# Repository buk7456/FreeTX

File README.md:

# FreeTX
Open source radio control system for almost anything.  
Remotely operate model airplanes, multicopters, helicopters, boats, land vehicles, robots, animatronics, etc.

## Main features
- 20 fully proportional RC channels, each encoded with 10 bits.
- Configurable RC channel output signal format.
- Update rate of 50x per second for all RC channels.
- Receiver binding, adjustable RF power, frequency hopping.
- Reverse, subtrim, endpoints, failsafe, dual rates and expo, custom curves, flight modes.
- Powerful mixer system, logical switches, function generators, counters, timers.
- Telemetry, alarms, warnings, notifications, home screen widgets, custom splash screen, etc.
- Model memory, I2C EEPROM and SD card supported. Model types, context-aware nomenclature.
- Intuitive user interface.

## Hardware and Schematics
The transmitter and receiver schematics can be found in the 'schematics' folder. 
The major components are
- 1x Atmega2560 microcontroller, 2x Atmega328p microcontrollers.
- 2x SX1276/77/78/79 or RFM95 based Lora modules. Other RF modules can possibly be used with some modifications to the source code.
- A 128x64 graphical LCD with KS0108 or ST7920 controller. Any other 128x64 LCD can however be used (provide own driver code).

## User interface
Three buttons are used for navigating the user interface i.e. Up, Select, Down. Long press Select to go Back.

## User guide
[User guide](doc/user_guide.md)  

A PDF version is also available [here.](https://raw.githubusercontent.com/buk7456/FreeTX/main/doc/FreeTX%20-%20User%20manual.pdf)

## Gallery

## Frequently Asked Questions
Got a question? [See the FAQ.](doc/faq.md)  

---

This project is based on an older project found [here.](https://github.com/buk7456/Arduino-LoRa-RC-transmitter-and-reciever)

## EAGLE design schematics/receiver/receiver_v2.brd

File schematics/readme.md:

This folder contains the EAGLE circuit schematics for the RC transmitter and receiver.

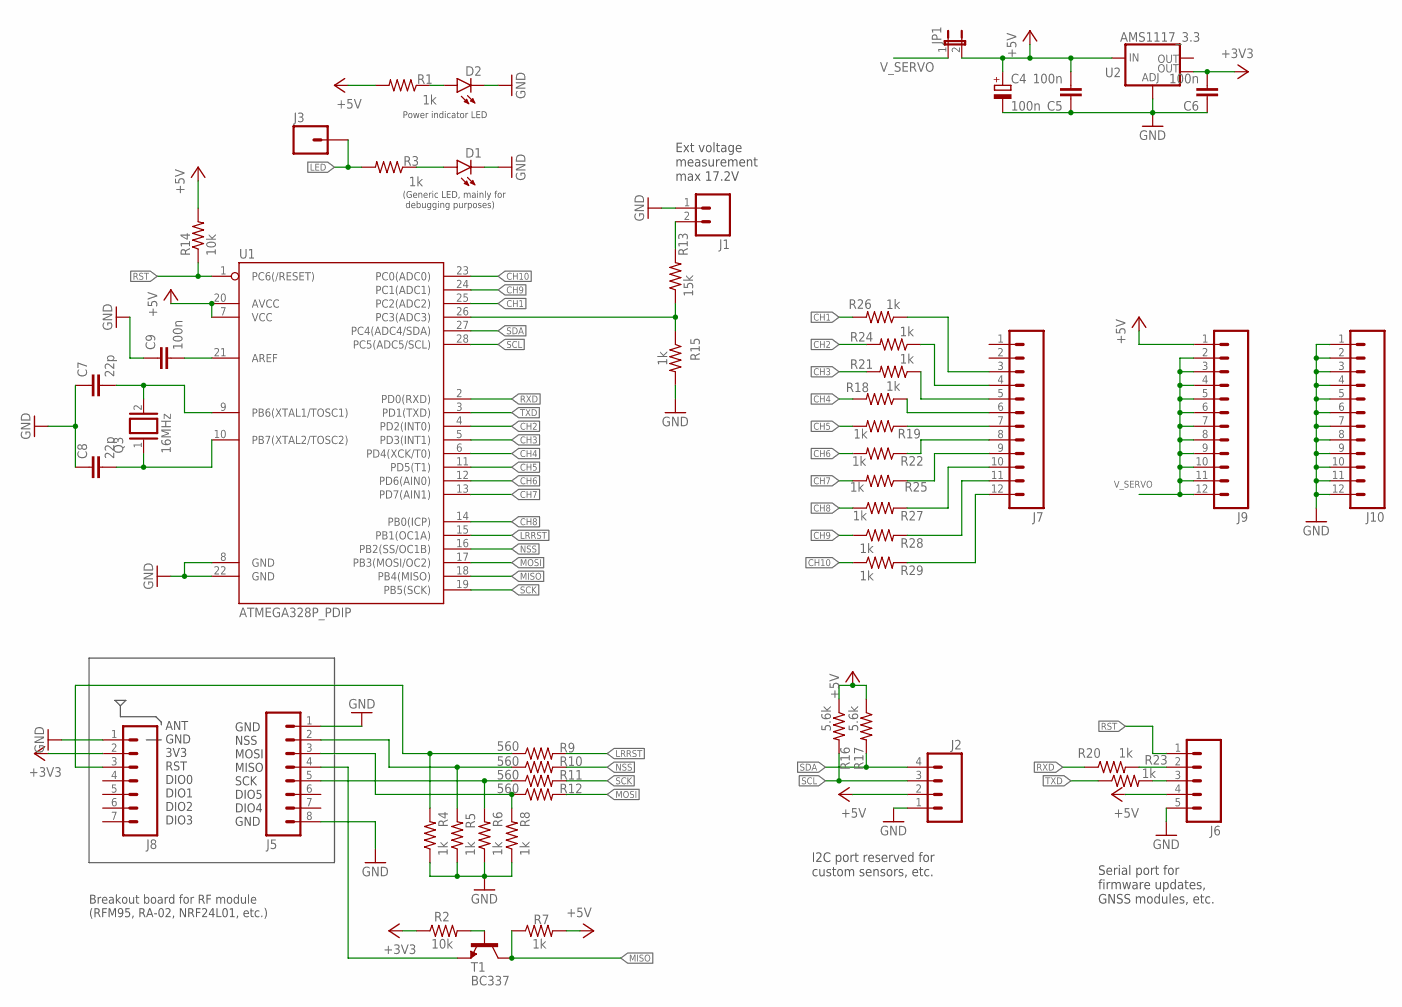
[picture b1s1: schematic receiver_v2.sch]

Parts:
C4: 100n; E2,5-6E
C5, C6, C9: 100n; C050-024X044
C7, C8: 22p; C050-024X044
D1, D2: LED3MM
J1: M02PTH; 1X02
J2: M04PTH; 1X04
J3: M01PTH; 1X01
J5: M08; 1X08_ROUND
J6: M05PTH; 1X05
J7, J9, J10: M12PTH; 1X12
J8: M07; 1X07
JP1: JP1E; JP1
Q3: 16MHz; QS
R1, R3, R4, R5, R6, R7, R8, R15, R18, R19, R21, R22, R24, R25, R26, R27, R28, R29: 1k; 0204V
R2: 10k; 0207/15
R9, R10, R11, R12: 560; 0204V
R13: 15k; 0204V
R14: 10k; 0204/7
R16, R17: 5.6k; 0204V
R20, R23: 1k; 0204/7
T1: BC337; TO92
U1: ATMEGA328P_PDIP; DIL28-3
U2: AMS1117_3.3; SOT223

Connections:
+3V3: C6.2, J8.2, R2.1, U2.4 (OUT)
+5V: C4.+, C5.2, J2.2, J6.4, J9.1, JP1.2, R1.2, R7.2, R14.2, R16.1, R17.1, U1.7 (VCC), U1.20 (AVCC), U2.3 (IN)
CH1: R26.2, U1.25 (PC2(ADC2))
CH2: R24.2, U1.4 (PD2(INT0))
CH3: R21.2, U1.5 (PD3(INT1))
CH4: R18.2, U1.6 (PD4(XCK/T0))
CH5: R19.2, U1.11 (PD5(T1))
CH6: R22.2, U1.12 (PD6(AIN0))
CH7: R25.2, U1.13 (PD7(AIN1))
CH8: R27.1, U1.14 (PB0(ICP))
CH9: R28.1, U1.24 (PC1(ADC1))
CH10: R29.1, U1.23 (PC0(ADC0))
GND: C4.-, C5.1, C6.1, C7.1, C8.1, C9.1, D1.K (C), D2.K (C), J1.1, J2.1, J5.1, J5.8, J6.5, J8.1, J10.1, J10.2, J10.3, J10.4, J10.5, J10.6, J10.7, J10.8, J10.9, J10.10, J10.11, J10.12, R4.1, R5.1, R6.1, R8.1, R15.2, U1.8 (GND), U1.22 (GND), U2.1 (ADJ)
LED: J3.1, R3.2
LRRST: R9.2, U1.15 (PB1(OC1A))
MISO: R7.1, T1.3 (C), U1.18 (PB4(MISO))
MOSI: R12.2, U1.17 (PB3(MOSI/OC2))
unnamed: D2.A, R1.1
unnamed: J7.11, R28.2
unnamed: J5.4, T1.1 (E)
unnamed: J7.10, R27.2
unnamed: J8.3, R4.2, R9.1
unnamed: J5.2, R5.2, R10.1
unnamed: J5.5, R6.2, R11.1
unnamed: J5.3, R8.2, R12.1
unnamed: C9.2, U1.21 (AREF)
unnamed: R13.1, R15.1, U1.26 (PC3(ADC3))
unnamed: J6.3, R23.2
unnamed: D1.A, R3.1
unnamed: C7.2, Q3.2, U1.9 (PB6(XTAL1/TOSC1))
unnamed: J7.3, R26.1
unnamed: C8.2, Q3.1, U1.10 (PB7(XTAL2/TOSC2))
unnamed: J6.2, R20.2
unnamed: J7.4, R24.1
unnamed: J7.5, R21.1
unnamed: J7.6, R18.1
unnamed: J7.7, R19.1
unnamed: J7.8, R22.1
unnamed: J7.9, R25.1
unnamed: R2.2, T1.2 (B)
unnamed: J1.2, R13.2
unnamed: J7.12, R29.2
NSS: R10.2, U1.16 (PB2(SS/OC1B))
RST: J6.1, R14.1, U1.1 (PC6(/RESET))
RXD: R20.1, U1.2 (PD0(RXD))
SCK: R11.2, U1.19 (PB5(SCK))
SCL: J2.3, R16.2, U1.28 (PC5(ADC5/SCL))
SDA: J2.4, R17.2, U1.27 (PC4(ADC4/SDA))
TXD: R23.1, U1.3 (PD1(TXD))
V_SERVO: J9.2, J9.3, J9.4, J9.5, J9.6, J9.7, J9.8, J9.9, J9.10, J9.11, J9.12, JP1.1

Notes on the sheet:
I2C port reserved for custom sensors, etc.
Serial port for firmware updates, GNSS modules, etc.
Ext voltage measurement max 17.2V
GND NSS MOSI MISO SCK DIO5 DIO4 GND
ANT GND 3V3 RST DIO0 DIO1 DIO2 DIO3
Breakout board for RF module (RFM95, RA-02, NRF24L01, etc.)
(Generic LED, mainly for debugging purposes)
Power indicator LED

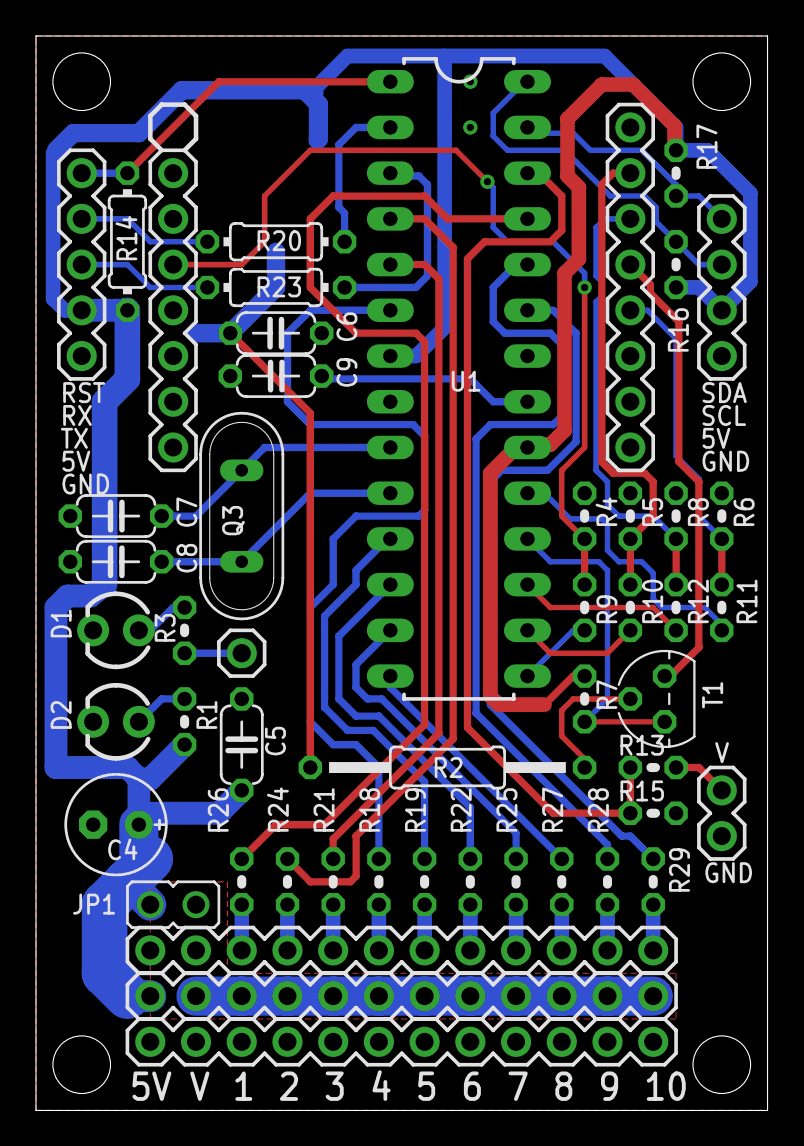
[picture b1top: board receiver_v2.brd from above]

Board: 2 copper layers, 40.6 x 59.7 mm, 51 parts (1 on the bottom side), 50 nets.

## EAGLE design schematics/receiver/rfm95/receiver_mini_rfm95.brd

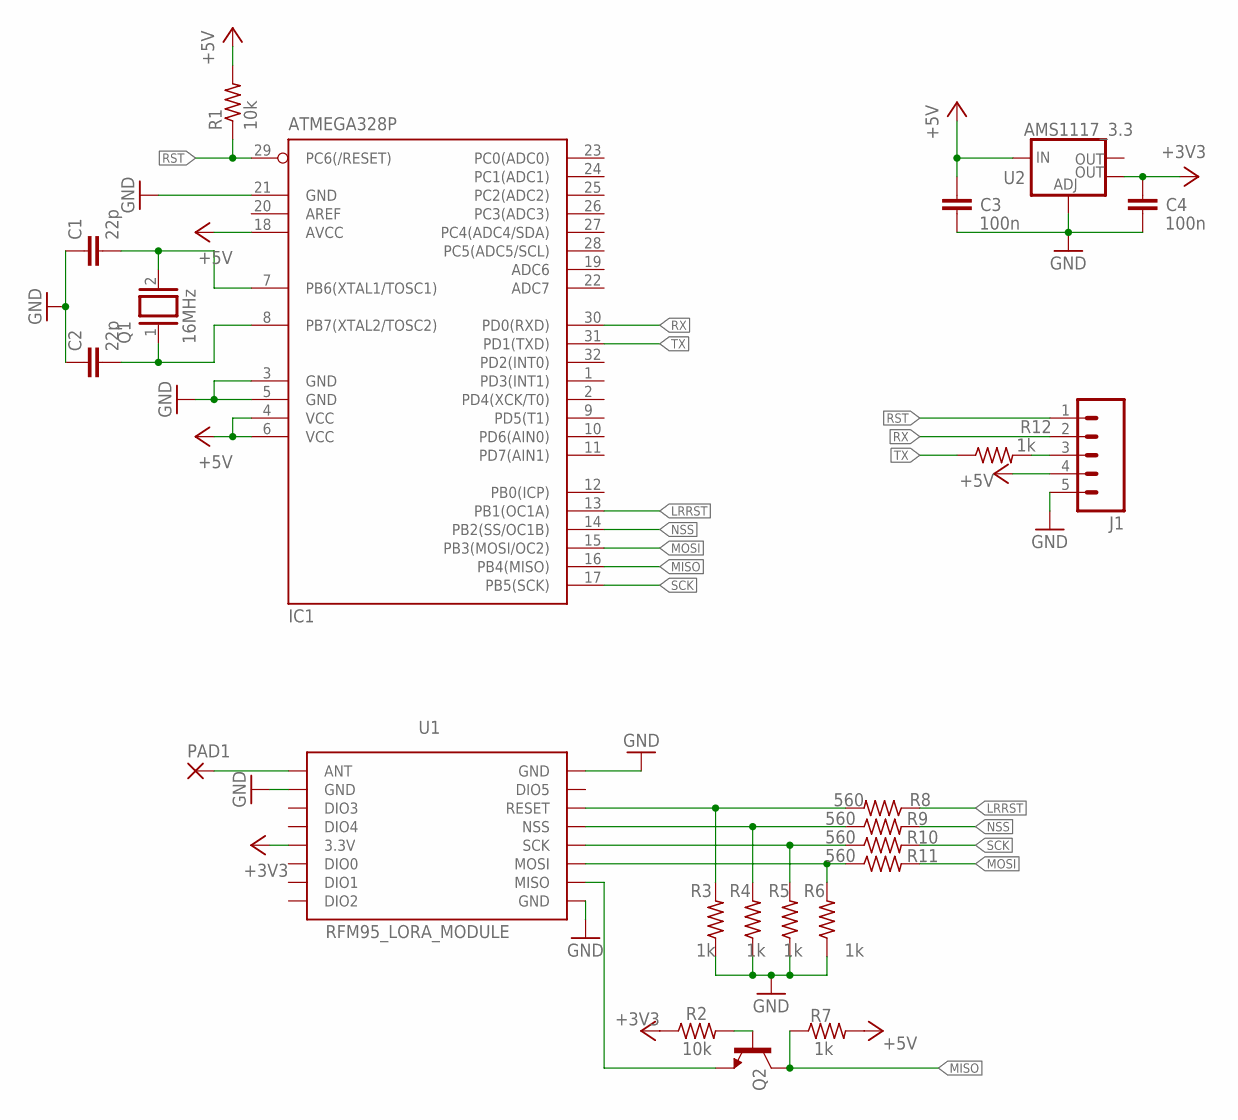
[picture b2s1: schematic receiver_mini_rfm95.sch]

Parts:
C1, C2: 22p; C0805K
C3, C4: 100n; C0805K
IC1: ATMEGA328P; TQFP32-08
J1: M05PTH; 1X05
PAD1: 2,15/1,0
Q1: 16MHz; QS
Q2: BC817-16SMD; SOT23-BEC
R1, R2: 10k; R0805
R3, R4, R5, R6, R7, R12: 1k; R0805
R8, R9, R10, R11: 560; R0805
U1: RFM95_LORA_MODULE; RFM95
U2: AMS1117_3.3; SOT223

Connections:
+3V3: C4.2, R2.1, U1.3.3V, U2.4 (OUT)
+5V: C3.2, IC1.4 (VCC), IC1.6 (VCC), IC1.18 (AVCC), J1.4, R1.2, R7.2, U2.3 (IN)
DIO3: U1.DIO3
GND: C1.1, C2.1, C3.1, C4.1, IC1.3 (GND), IC1.5 (GND), IC1.21 (GND), J1.5, R3.1, R4.1, R5.1, R6.1, U1.GND, U1.GND@1 (GND), U1.GND@2 (GND), U2.1 (ADJ)
LRRST: IC1.13 (PB1(OC1A)), R8.1
MISO: IC1.16 (PB4(MISO)), Q2.C, R7.1
MOSI: IC1.15 (PB3(MOSI/OC2)), R11.2
unnamed: C1.2, IC1.7 (PB6(XTAL1/TOSC1)), Q1.2
unnamed: J1.3, R12.2
unnamed: C2.2, IC1.8 (PB7(XTAL2/TOSC2)), Q1.1
unnamed: R3.2, R8.2, U1.RESET
unnamed: Q2.E, U1.MISO
unnamed: R4.2, R9.1, U1.NSS
unnamed: R5.2, R10.1, U1.SCK
unnamed: R6.2, R11.1, U1.MOSI
unnamed: PAD1.1, U1.ANT
unnamed: Q2.B, R2.2
NSS: IC1.14 (PB2(SS/OC1B)), R9.2
RST: IC1.29 (PC6(/RESET)), J1.1, R1.1
RX: IC1.30 (PD0(RXD)), J1.2
SCK: IC1.17 (PB5(SCK)), R10.2
TX: IC1.31 (PD1(TXD)), R12.1

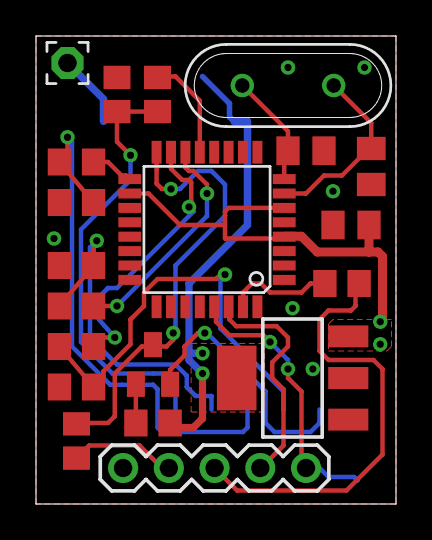
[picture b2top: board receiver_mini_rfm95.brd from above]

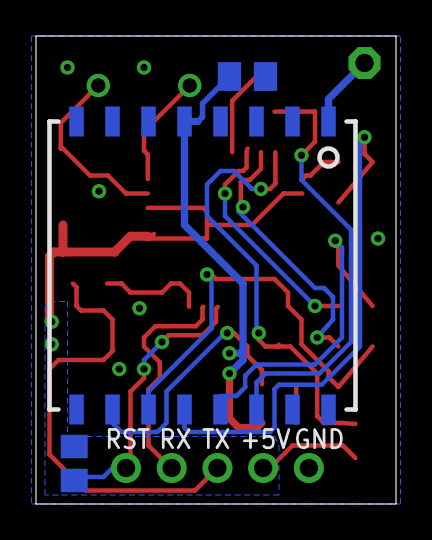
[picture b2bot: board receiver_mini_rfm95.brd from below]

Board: 2 copper layers, 20.0 x 26.0 mm, 23 parts (3 on the bottom side), 21 nets.

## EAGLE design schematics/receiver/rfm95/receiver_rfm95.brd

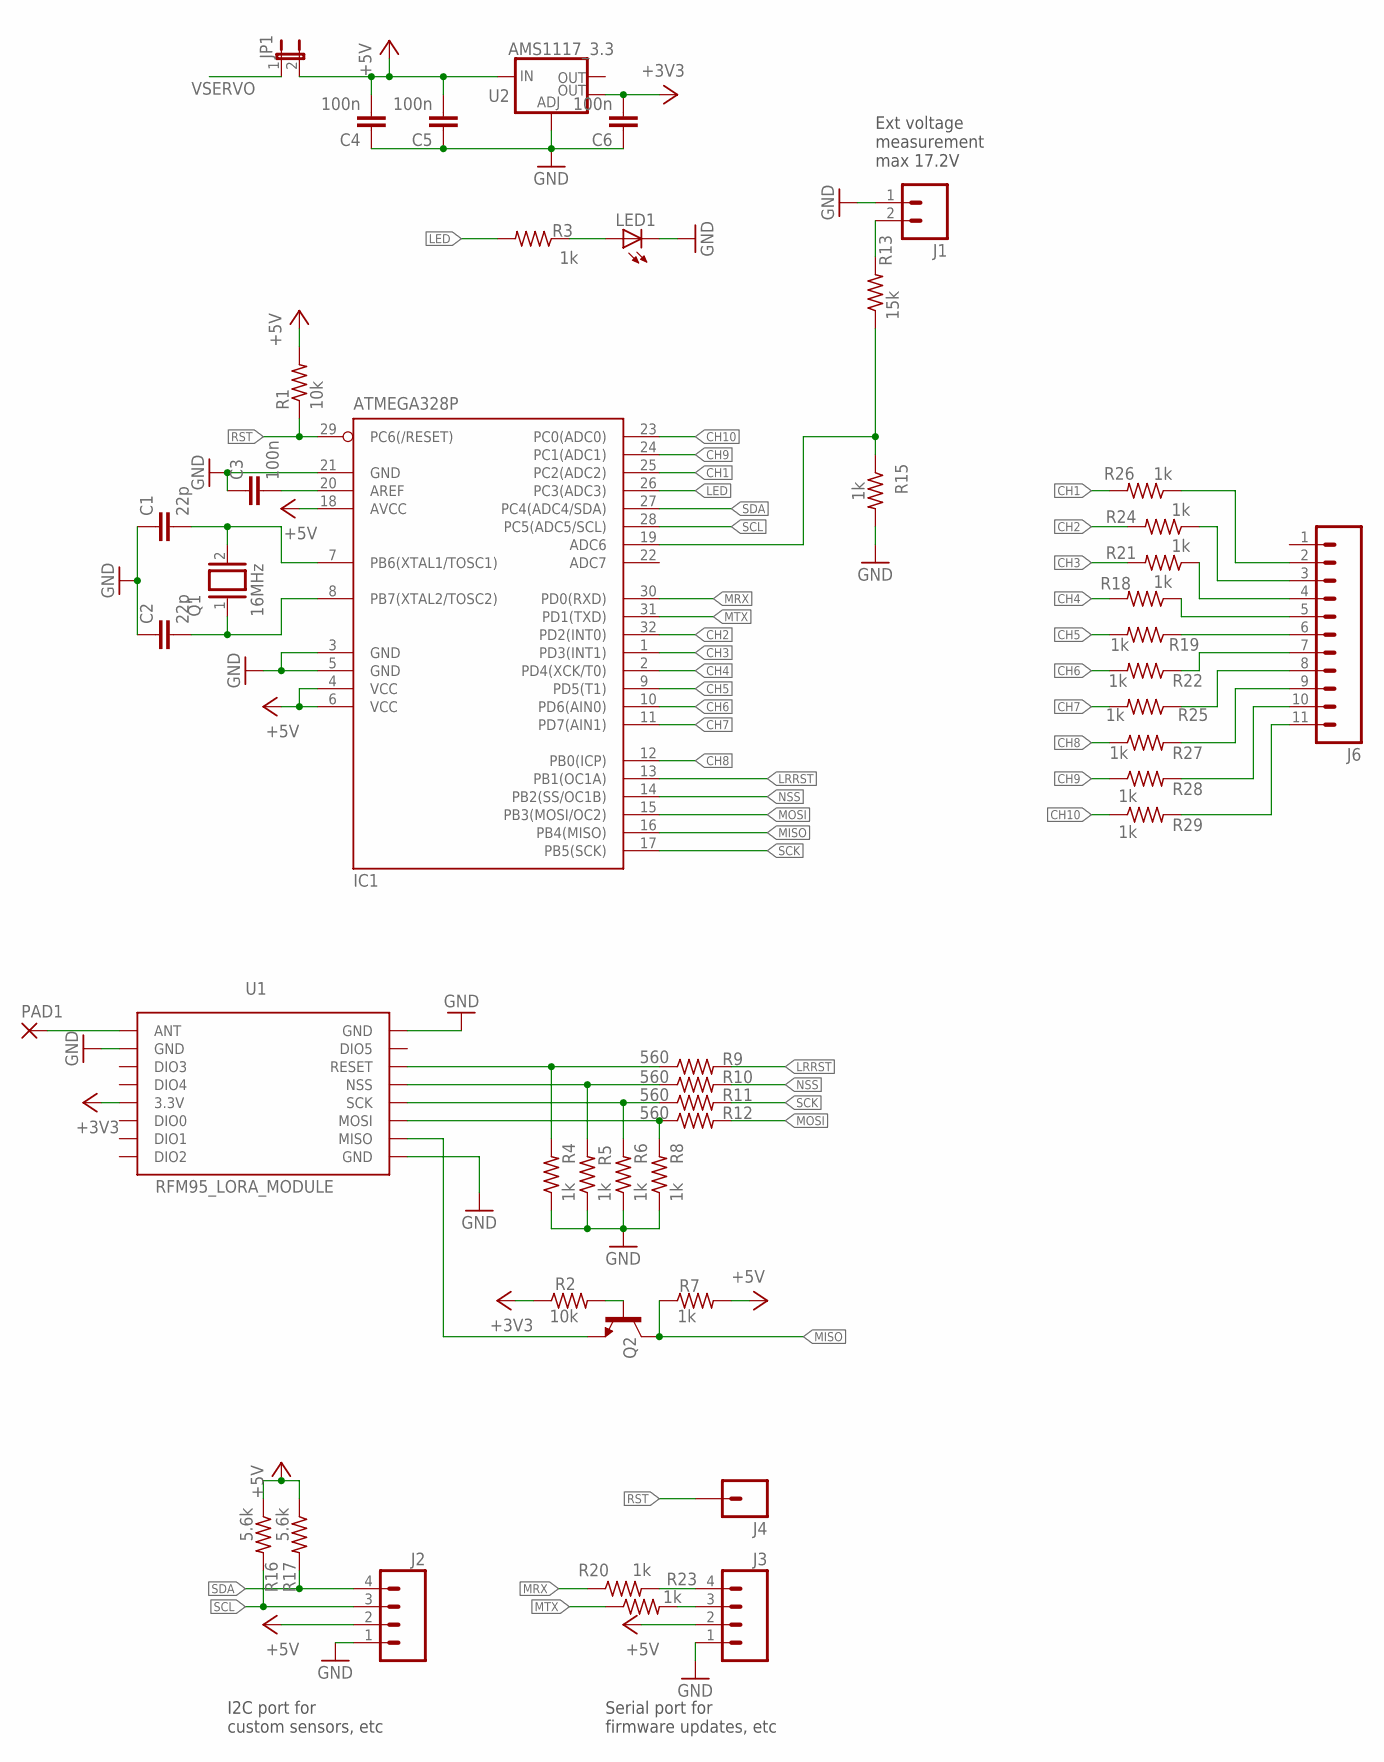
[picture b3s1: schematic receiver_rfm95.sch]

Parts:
C1, C2: 22p; C0805K
C3, C4, C5, C6: 100n; C0805K
IC1: ATMEGA328P; TQFP32-08
J1: M02PTH; 1X02
J2, J3: M04PTH; 1X04
J4: M01PTH; 1X01
J6: M11PTH; 1X11
JP1: JP1E; JP1
LED1: LEDCHIPLED_1206; CHIPLED_1206
PAD1: 2,15/1,0
Q1: 16MHz; QS
Q2: BC817-16SMD; SOT23-BEC
R1, R2: 10k; R0805
R3, R4, R5, R6, R7, R8, R15, R18, R19, R20, R21, R22, R23, R24, R25, R26, R27, R28, R29: 1k; R0805
R9, R10, R11, R12: 560; R0805
R13: 15k; R0805
R16, R17: 5.6k; R0805
U1: RFM95_LORA_MODULE; RFM95
U2: AMS1117_3.3; SOT223

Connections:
+3V3: C6.2, R2.1, U1.3.3V, U2.4 (OUT)
+5V: C4.2, C5.2, IC1.4 (VCC), IC1.6 (VCC), IC1.18 (AVCC), J2.2, J3.2, JP1.2, R1.2, R7.2, R16.1, R17.1, U2.3 (IN)
CH1: IC1.25 (PC2(ADC2)), R26.2
CH2: IC1.32 (PD2(INT0)), R24.2
CH3: IC1.1 (PD3(INT1)), R21.2
CH4: IC1.2 (PD4(XCK/T0)), R18.2
CH5: IC1.9 (PD5(T1)), R19.2
CH6: IC1.10 (PD6(AIN0)), R22.2
CH7: IC1.11 (PD7(AIN1)), R25.2
CH8: IC1.12 (PB0(ICP)), R27.1
CH9: IC1.24 (PC1(ADC1)), R28.1
CH10: IC1.23 (PC0(ADC0)), R29.1
DIO3: U1.DIO3
GND: C1.1, C2.1, C3.1, C4.1, C5.1, C6.1, IC1.3 (GND), IC1.5 (GND), IC1.21 (GND), J1.1, J2.1, J3.1, LED1.C, R4.1, R5.1, R6.1, R8.1, R15.2, U1.GND, U1.GND@1 (GND), U1.GND@2 (GND), U2.1 (ADJ)
LED: IC1.26 (PC3(ADC3)), R3.2
LRRST: IC1.13 (PB1(OC1A)), R9.2
MISO: IC1.16 (PB4(MISO)), Q2.C, R7.1
MOSI: IC1.15 (PB3(MOSI/OC2)), R12.2
MRX: IC1.30 (PD0(RXD)), R20.1
MTX: IC1.31 (PD1(TXD)), R23.1
unnamed: C1.2, IC1.7 (PB6(XTAL1/TOSC1)), Q1.2
unnamed: J6.10, R28.2
unnamed: C2.2, IC1.8 (PB7(XTAL2/TOSC2)), Q1.1
unnamed: J6.9, R27.2
unnamed: R4.2, R9.1, U1.RESET
unnamed: R5.2, R10.1, U1.NSS
unnamed: R6.2, R11.1, U1.SCK
unnamed: R8.2, R12.1, U1.MOSI
unnamed: Q2.E, U1.MISO
unnamed: C3.2, IC1.20 (AREF)
unnamed: IC1.19 (ADC6), R13.1, R15.1
unnamed: J3.3, R23.2
unnamed: LED1.A, R3.1
unnamed: PAD1.1, U1.ANT
unnamed: J6.2, R26.1
unnamed: J3.4, R20.2
unnamed: J6.3, R24.1
unnamed: J6.4, R21.1
unnamed: J6.5, R18.1
unnamed: J6.6, R19.1
unnamed: J6.7, R22.1
unnamed: J6.8, R25.1
unnamed: Q2.B, R2.2
unnamed: J1.2, R13.2
unnamed: J6.11, R29.2
NSS: IC1.14 (PB2(SS/OC1B)), R10.2
RST: IC1.29 (PC6(/RESET)), J4.1, R1.1
SCK: IC1.17 (PB5(SCK)), R11.2
SCL: IC1.28 (PC5(ADC5/SCL)), J2.3, R16.2
SDA: IC1.27 (PC4(ADC4/SDA)), J2.4, R17.2
VSERVO: JP1.1

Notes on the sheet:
I2C port for custom sensors, etc
Serial port for firmware updates, etc
Ext voltage measurement max 17.2V

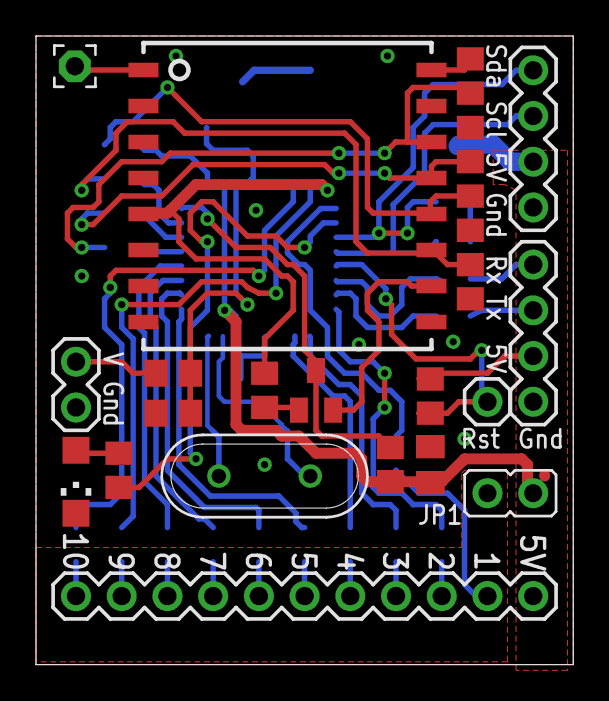
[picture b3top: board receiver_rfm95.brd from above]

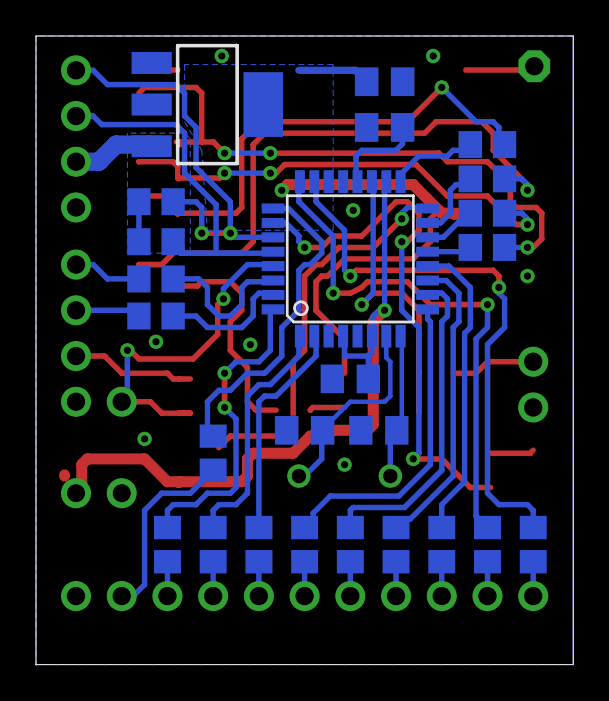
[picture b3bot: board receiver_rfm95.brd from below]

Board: 2 copper layers, 29.8 x 34.9 mm, 47 parts (25 on the bottom side), 49 nets.

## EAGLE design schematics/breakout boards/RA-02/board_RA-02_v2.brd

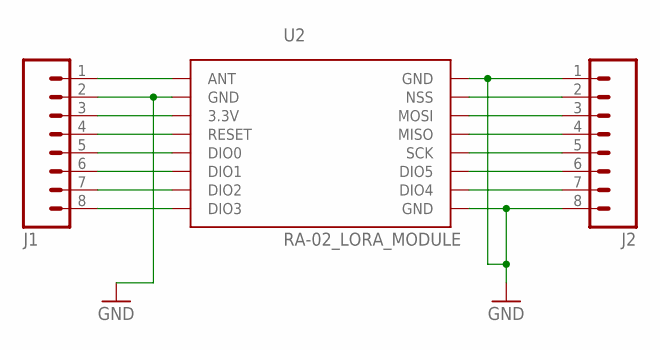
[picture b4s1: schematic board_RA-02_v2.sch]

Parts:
J1, J2: M08; 1X08_ROUND
U2: RA-02_LORA_MODULE; RA-02

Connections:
ANT: J1.1, U2.ANT
GND: J1.2, J2.1, J2.8, U2.GND@2 (GND), U2.GND@3 (GND), U2.GND@4 (GND)
unnamed: J1.3, U2.3.3V
unnamed: J1.4, U2.RESET
unnamed: J1.5, U2.DIO0
unnamed: J1.6, U2.DIO1
unnamed: J1.7, U2.DIO2
unnamed: J1.8, U2.DIO3
unnamed: J2.2, U2.NSS
unnamed: J2.3, U2.MOSI
unnamed: J2.4, U2.MISO
unnamed: J2.5, U2.SCK
unnamed: J2.6, U2.DIO5
unnamed: J2.7, U2.DIO4

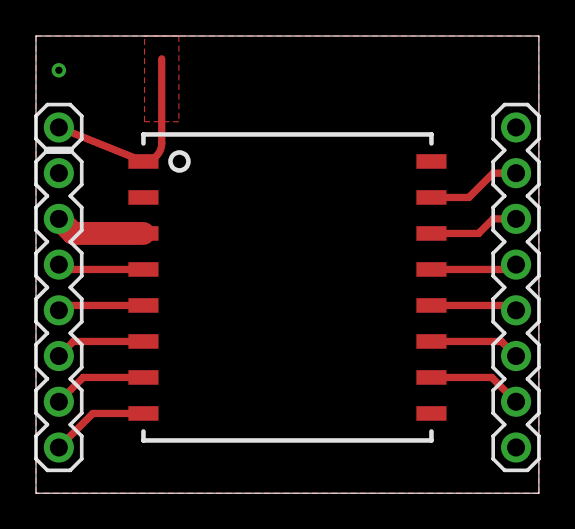
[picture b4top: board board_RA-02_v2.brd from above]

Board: 2 copper layers, 27.9 x 25.4 mm, 3 parts (0 on the bottom side), 14 nets.

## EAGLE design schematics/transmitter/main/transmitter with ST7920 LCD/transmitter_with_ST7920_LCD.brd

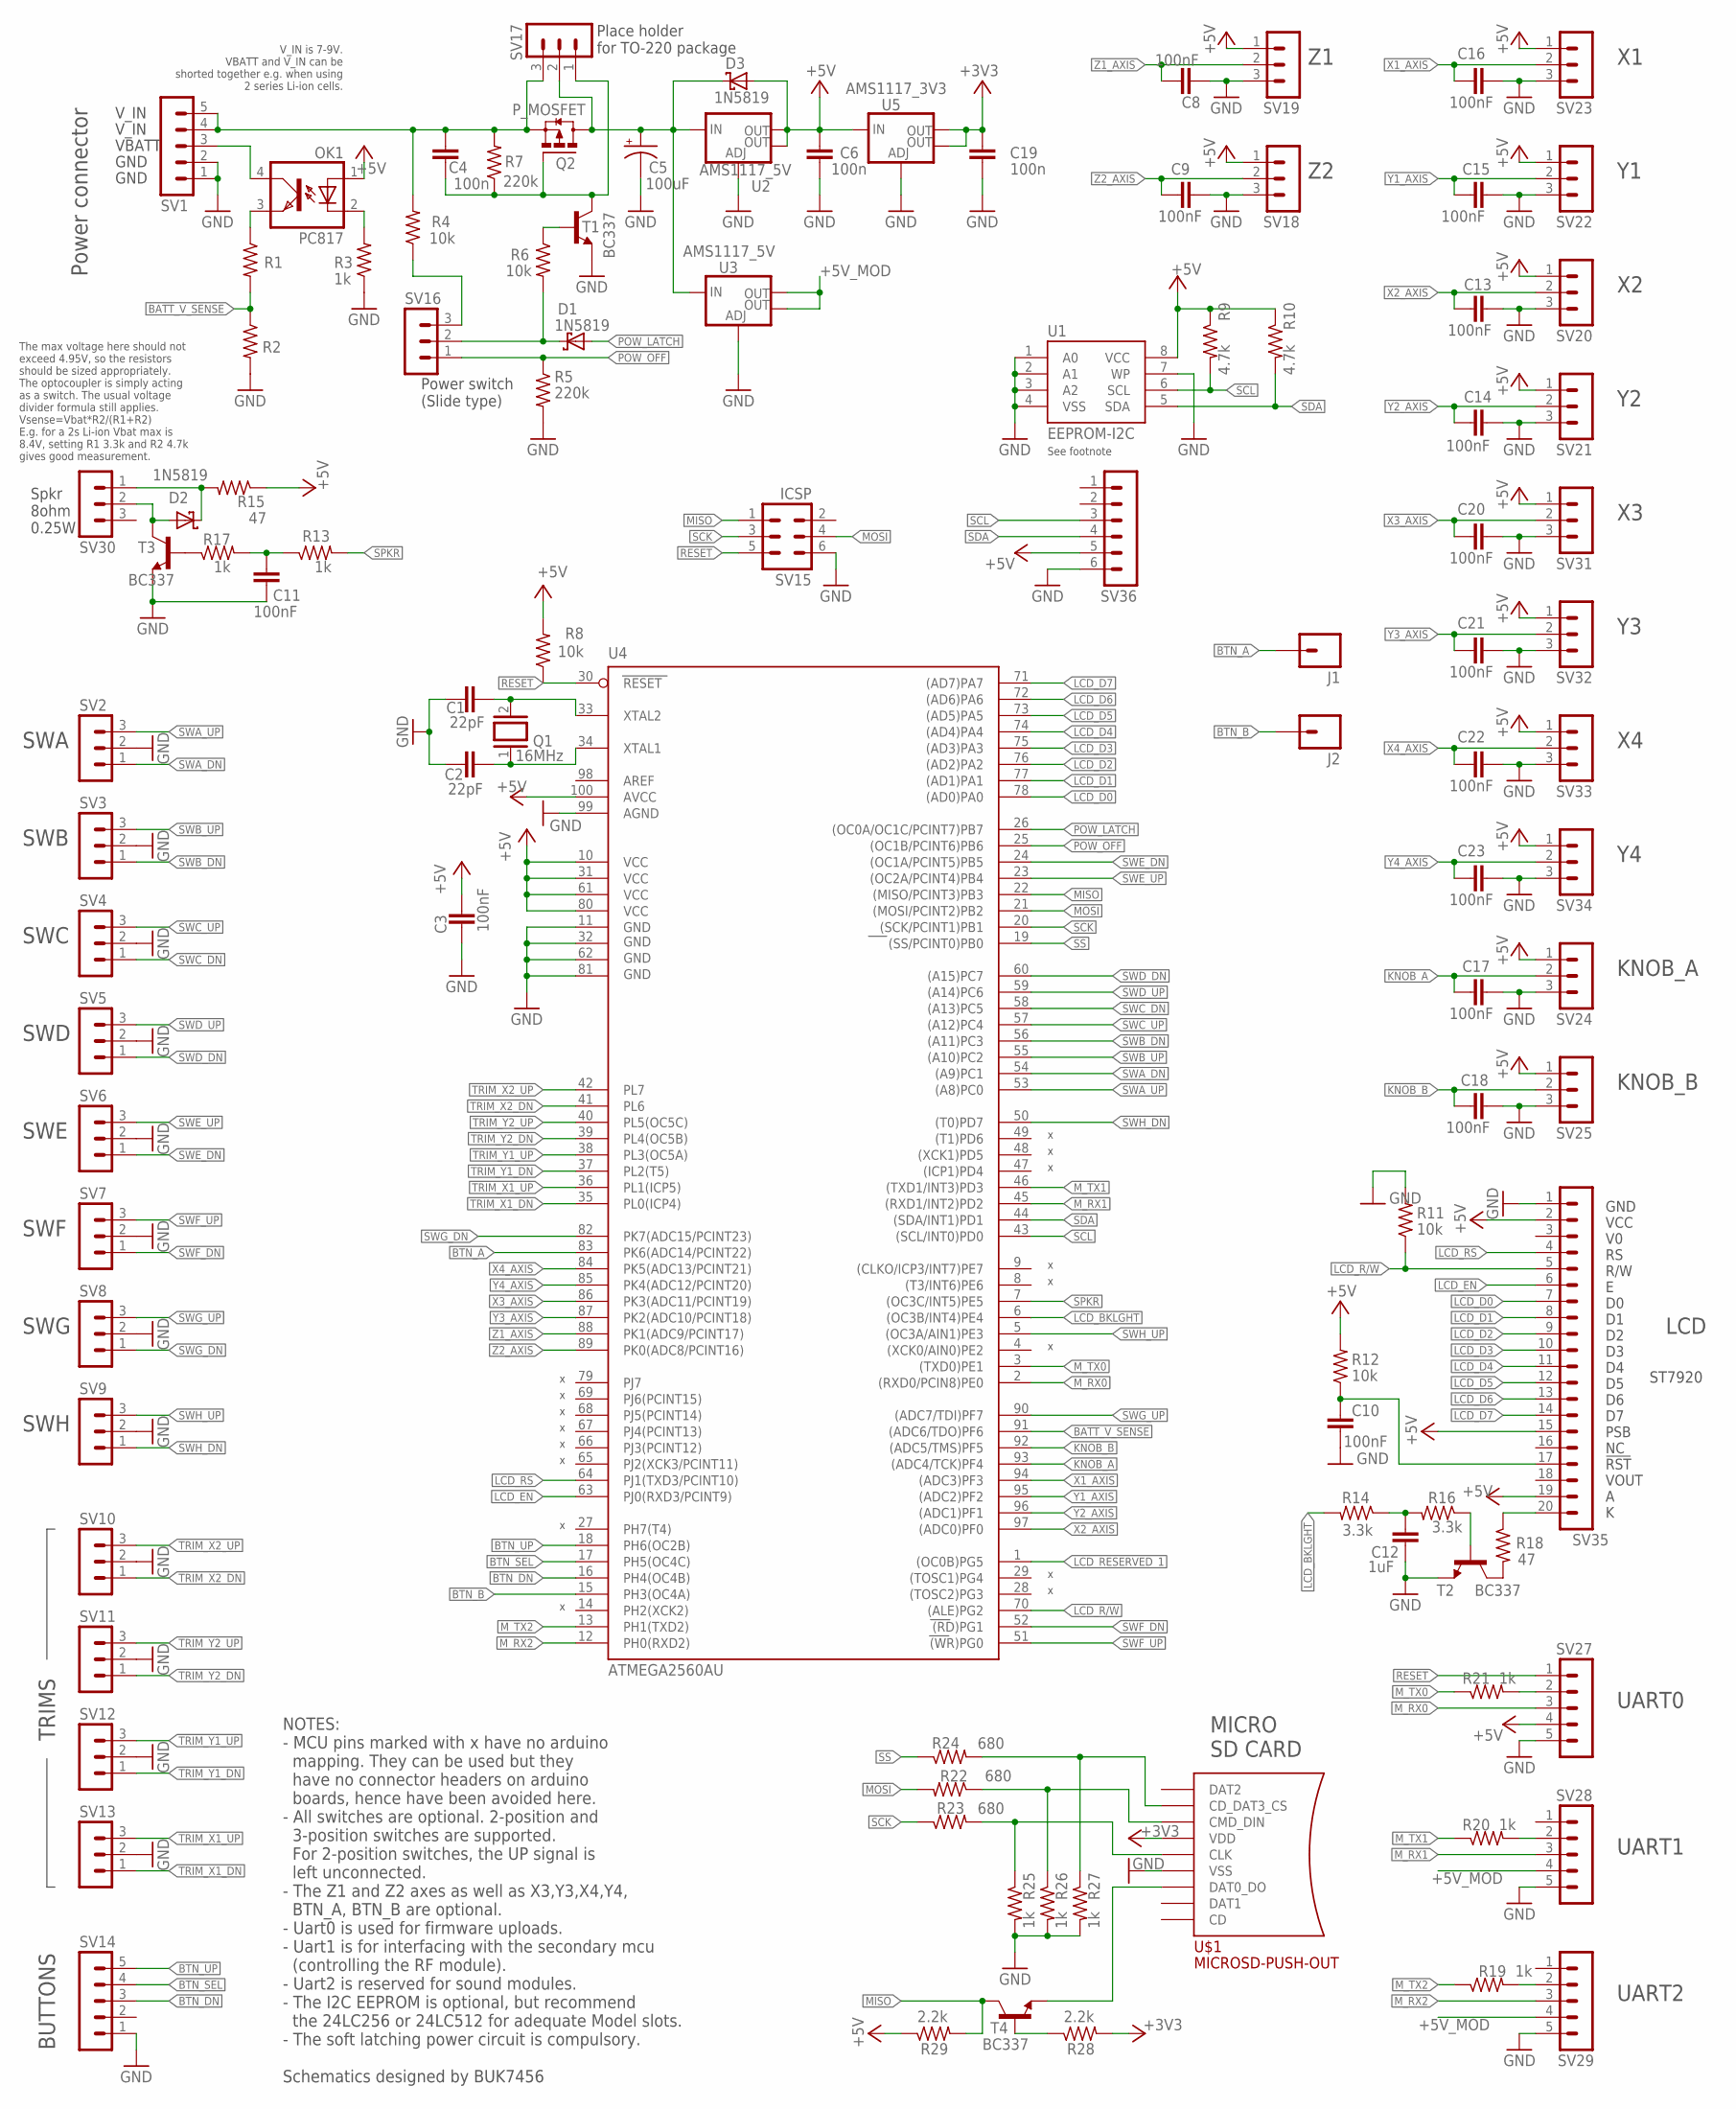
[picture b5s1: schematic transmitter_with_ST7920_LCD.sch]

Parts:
C1, C2: 22pF; C050-024X044
C3, C8, C9, C10, C11, C13, C14, C15, C16, C17, C18, C20, C21, C22, C23: 100nF; C050-024X044
C4, C6, C19: 100n; C050-024X044
C5: 100uF; E2,5-6E
C12: 1uF; C050-024X044
D1, D2, D3: 1N5819; DO41-7.6
J1, J2: M01PTH_LONGPAD; 1X01_LONGPAD
OK1: PC817; DIL04
Q1: 16MHz; QS
Q2: P_MOSFET; SUPER-SOT3
R1, R2, R3, R13, R17, R19, R20, R21, R25, R26, R27: 1k; 0204/5
R4, R6, R8, R11, R12: 10k; 0204/5
R5, R7: 220k; 0204/5
R9, R10: 4.7k; 0204/5
R14, R16: 3.3k; 0204/5
R15, R18: 47; 0204/5
R22, R23, R24: 680; 0204/5
R28, R29: 2.2k; 0204/5
SV1, SV14, SV27, SV28, SV29: MA05-1
SV2, SV3, SV4, SV5, SV6, SV7, SV8, SV9, SV10, SV11, SV12, SV13, SV16, SV17, SV18, SV19, SV20, SV21, SV22, SV23, SV24, SV25, SV30, SV31, SV32, SV33, SV34: MA03-1
SV15: ICSP; MA03-2
SV35: MA20-1
SV36: MA06-1
T1, T2, T3, T4: BC337; TO92
U1: EEPROM-I2C; SO08-EIAJ
U2, U3: AMS1117_5V; SOT223
U4: ATMEGA2560AU; TQFP100
U5: AMS1117_3V3; SOT223
U$1: MICROSD-PUSH-OUT

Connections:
+3V3: C19.2, R28.2, U5.2 (OUT), U5.4 (OUT), U$1.4 (VDD)
+5V: C3.1, C6.2, D3.A, OK1.1 (A), R8.2, R9.1, R10.1, R12.2, R15.1, R29.1, SV18.1, SV19.1, SV20.1, SV21.1, SV22.1, SV23.1, SV24.1, SV25.1, SV27.4, SV31.1, SV32.1, SV33.1, SV34.1, SV35.2, SV35.15, SV35.19, SV36.5, U1.8 (VCC), U2.2 (OUT), U2.4 (OUT), U4.10 (VCC), U4.31 (VCC1), U4.61 (VCC2), U4.80 (VCC3), U4.100 (AVCC), U5.3 (IN)
+5V_MOD: SV28.4, SV29.4, U3.2 (OUT), U3.4 (OUT)
BATT_V_SENSE: R1.2, R2.1, U4.91 ((ADC6/TDO)PF6)
BTN_A: J1.1, U4.83 (PK6(ADC14/PCINT22))
BTN_B: J2.1, U4.15 (PH3(OC4A))
BTN_DN: SV14.3, U4.16 (PH4(OC4B))
BTN_SEL: SV14.4, U4.17 (PH5(OC4C))
BTN_UP: SV14.5, U4.18 (PH6(OC2B))
GND: C1.1, C2.1, C3.2, C5.-, C6.1, C8.2, C9.1, C10.2, C11.2, C12.2, C13.1, C14.1, C15.1, C16.1, C17.1, C18.1, C19.1, C20.1, C21.1, C22.1, C23.1, R2.2, R3.1, R5.2, R11.2, R25.2, R26.2, R27.2, SV1.1, SV1.2, SV2.2, SV3.2, SV4.2, SV5.2, SV6.2, SV7.2, SV8.2, SV9.2, SV10.2, SV11.2, SV12.2, SV13.2, SV14.1, SV15.6, SV18.3, SV19.3, SV20.3, SV21.3, SV22.3, SV23.3, SV24.3, SV25.3, SV27.5, SV28.5, SV29.5, SV31.3, SV32.3, SV33.3, SV34.3, SV35.1, SV36.6, T1.1 (E), T2.1 (E), T3.1 (E), U1.1 (A0), U1.2 (A1), U1.3 (A2), U1.4 (VSS), U1.7 (WP), U2.1 (ADJ), U3.1 (ADJ), U4.11 (GND), U4.32 (GND1), U4.62 (GND2), U4.81 (GND3), U4.99 (AGND), U5.1 (ADJ), U$1.6 (VSS), U$1.G1 (VSS), U$1.G2 (VSS), U$1.G3 (VSS), U$1.G4 (VSS)
KNOB_A: C17.2, SV24.2, U4.93 ((ADC4/TCK)PF4)
KNOB_B: C18.2, SV25.2, U4.92 ((ADC5/TMS)PF5)
LCD_BKLGHT: R14.2, U4.6 ((OC3B/INT4)PE4)
LCD_D0: SV35.7, U4.78 ((AD0)PA0)
LCD_D1: SV35.8, U4.77 ((AD1)PA1)
LCD_D2: SV35.9, U4.76 ((AD2)PA2)
LCD_D3: SV35.10, U4.75 ((AD3)PA3)
LCD_D4: SV35.11, U4.74 ((AD4)PA4)
LCD_D5: SV35.12, U4.73 ((AD5)PA5)
LCD_D6: SV35.13, U4.72 ((AD6)PA6)
LCD_D7: SV35.14, U4.71 ((AD7)PA7)
LCD_EN: SV35.6, U4.63 (PJ0(RXD3/PCINT9))
LCD_R/W: R11.1, SV35.5, U4.70 ((ALE)PG2)
LCD_RESERVED_1: U4.1 ((OC0B)PG5)
LCD_RS: SV35.4, U4.64 (PJ1(TXD3/PCINT10))
MISO: R29.2, SV15.1, T4.3 (C), U4.22 ((MISO/PCINT3)PB3)
MOSI: R22.2, SV15.4, U4.21 ((MOSI/PCINT2)PB2)
M_RX0: SV27.3, U4.2 ((RXD0/PCIN8)PE0)
M_RX1: SV28.3, U4.45 ((RXD1/INT2)PD2)
M_RX2: SV29.3, U4.12 (PH0(RXD2))
M_TX0: R21.1, U4.3 ((TXD0)PE1)
M_TX1: R20.1, U4.46 ((TXD1/INT3)PD3)
M_TX2: R19.1, U4.13 (PH1(TXD2))
unnamed: C12.1, R14.1, R16.2
unnamed: C10.1, R12.1, SV35.17
unnamed: R18.2, T2.3 (C)
unnamed: R16.1, T2.2 (B)
unnamed: C11.1, R13.1, R17.2
unnamed: R21.2, SV27.2
unnamed: R20.2, SV28.2
unnamed: R19.2, SV29.2
unnamed: C1.2, Q1.2, U4.33 (XTAL2)
unnamed: C2.2, Q1.1, U4.34 (XTAL1)
unnamed: T4.1 (E), U$1.7 (DAT0_DO)
unnamed: OK1.4 (COL), SV1.3
unnamed: R18.1, SV35.20
unnamed: R24.2, R27.1, U$1.2 (CD_DAT3_CS)
unnamed: R22.1, R26.1, U$1.3 (CMD_DIN)
unnamed: R23.2, R25.1, U$1.5 (CLK)
unnamed: R28.1, T4.2 (B)
unnamed: R17.1, T3.2 (B)
unnamed: D2.A, SV30.2, T3.3 (C)
unnamed: D2.C, R15.2, SV30.1
unnamed: R6.1, T1.2 (B)
unnamed: D1.C, R6.2, SV16.2
unnamed: OK1.3 (EMIT), R1.1
unnamed: C4.2, Q2.2 (S), R4.2, R7.2, SV1.4, SV1.5, SV17.3
unnamed: C4.1, Q2.1 (G), R7.1, SV17.1, T1.3 (C)
unnamed: OK1.2 (C), R3.2
unnamed: R4.1, SV16.3
unnamed: C5.+, D3.C, Q2.3 (D), SV17.2, U2.3 (IN), U3.3 (IN)
POW_LATCH: D1.A, U4.26 ((OC0A/OC1C/PCINT7)PB7)
POW_OFF: R5.1, SV16.1, U4.25 ((OC1B/PCINT6)PB6)
RESET: R8.1, SV15.5, SV27.1, U4.30 (RESET)
SCK: R23.1, SV15.3, U4.20 ((SCK/PCINT1)PB1)
SCL: R9.2, SV36.3, U1.6 (SCL), U4.43 ((SCL/INT0)PD0)
SDA: R10.2, SV36.4, U1.5 (SDA), U4.44 ((SDA/INT1)PD1)
SPKR: R13.2, U4.7 ((OC3C/INT5)PE5)
SS: R24.1, U4.19 ((SS/PCINT0)PB0)
SWA_DN: SV2.1, U4.54 ((A9)PC1)
SWA_UP: SV2.3, U4.53 ((A8)PC0)
SWB_DN: SV3.1, U4.56 ((A11)PC3)
SWB_UP: SV3.3, U4.55 ((A10)PC2)
SWC_DN: SV4.1, U4.58 ((A13)PC5)
SWC_UP: SV4.3, U4.57 ((A12)PC4)
SWD_DN: SV5.1, U4.60 ((A15)PC7)
SWD_UP: SV5.3, U4.59 ((A14)PC6)
SWE_DN: SV6.1, U4.24 ((OC1A/PCINT5)PB5)
SWE_UP: SV6.3, U4.23 ((OC2A/PCINT4)PB4)
SWF_DN: SV7.1, U4.52 ((RD)PG1)
SWF_UP: SV7.3, U4.51 ((WR)PG0)
SWG_DN: SV8.1, U4.82 (PK7(ADC15/PCINT23))
SWG_UP: SV8.3, U4.90 ((ADC7/TDI)PF7)
SWH_DN: SV9.1, U4.50 ((T0)PD7)
SWH_UP: SV9.3, U4.5 ((OC3A/AIN1)PE3)
TRIM_X1_DN: SV13.1, U4.35 (PL0(ICP4))
TRIM_X1_UP: SV13.3, U4.36 (PL1(ICP5))
TRIM_X2_DN: SV10.1, U4.41 (PL6)
TRIM_X2_UP: SV10.3, U4.42 (PL7)
TRIM_Y1_DN: SV12.1, U4.37 (PL2(T5))
TRIM_Y1_UP: SV12.3, U4.38 (PL3(OC5A))
TRIM_Y2_DN: SV11.1, U4.39 (PL4(OC5B))
TRIM_Y2_UP: SV11.3, U4.40 (PL5(OC5C))
X1_AXIS: C16.2, SV23.2, U4.94 ((ADC3)PF3)
X2_AXIS: C13.2, SV20.2, U4.97 ((ADC0)PF0)
X3_AXIS: C20.2, SV31.2, U4.86 (PK3(ADC11/PCINT19))
X4_AXIS: C22.2, SV33.2, U4.84 (PK5(ADC13/PCINT21))
Y1_AXIS: C15.2, SV22.2, U4.95 ((ADC2)PF2)
Y2_AXIS: C14.2, SV21.2, U4.96 ((ADC1)PF1)
Y3_AXIS: C21.2, SV32.2, U4.87 (PK2(ADC10/PCINT18))
Y4_AXIS: C23.2, SV34.2, U4.85 (PK4(ADC12/PCINT20))
Z1_AXIS: C8.1, SV19.2, U4.88 (PK1(ADC9/PCINT17))
Z2_AXIS: C9.2, SV18.2, U4.89 (PK0(ADC8/PCINT16))

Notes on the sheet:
Spkr 8ohm 0.25W
GND
VBATT
Power connector
The max voltage here should not exceed 4.95V, so the resistors should be sized appropriately. The optocoupler is simply acting as a switch. The usual voltage divider formula still applies. Vsense=Vbat*R2/(R1+R2) E.g. for a 2s Li-ion Vbat max is 8.4V, setting R1 3.3k and R2 4.7k gives good measureme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
Power switch (Slide type)
V_IN
V_IN is 7-9V. VBATT and V_IN can be shorted together e.g. when using 2 series Li-ion cells.
SWA
SWB
SWC
SWD
SWE
SWF
SWG
SWH
LCD
UART0
UART1
BUTTONS
TRIMS
KNOB_A
KNOB_B
NOTES: - MCU pins marked with x have no arduino mapping. They can be used but they have no connector headers on arduino boards, hence have been avoided here. - All switches are optional. 2-position and 3-position switches are supported. For 2-position switches, the UP signal is left unconnected. - 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
Place holder for TO-220 package
UART2
MICRO SD CARD
See footnote
GND VCC V0 RS R/W E D0 D1 D2 D3 D4 D5 D6 D7 PSB NC !RST VOUT A K
ST7920

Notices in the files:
parts and their libraries:
SparkFun-Connectors: Licensing: Creative Commons ShareAlike 4.0 International - https://creativecommons.org/licenses/by-sa/4.0
